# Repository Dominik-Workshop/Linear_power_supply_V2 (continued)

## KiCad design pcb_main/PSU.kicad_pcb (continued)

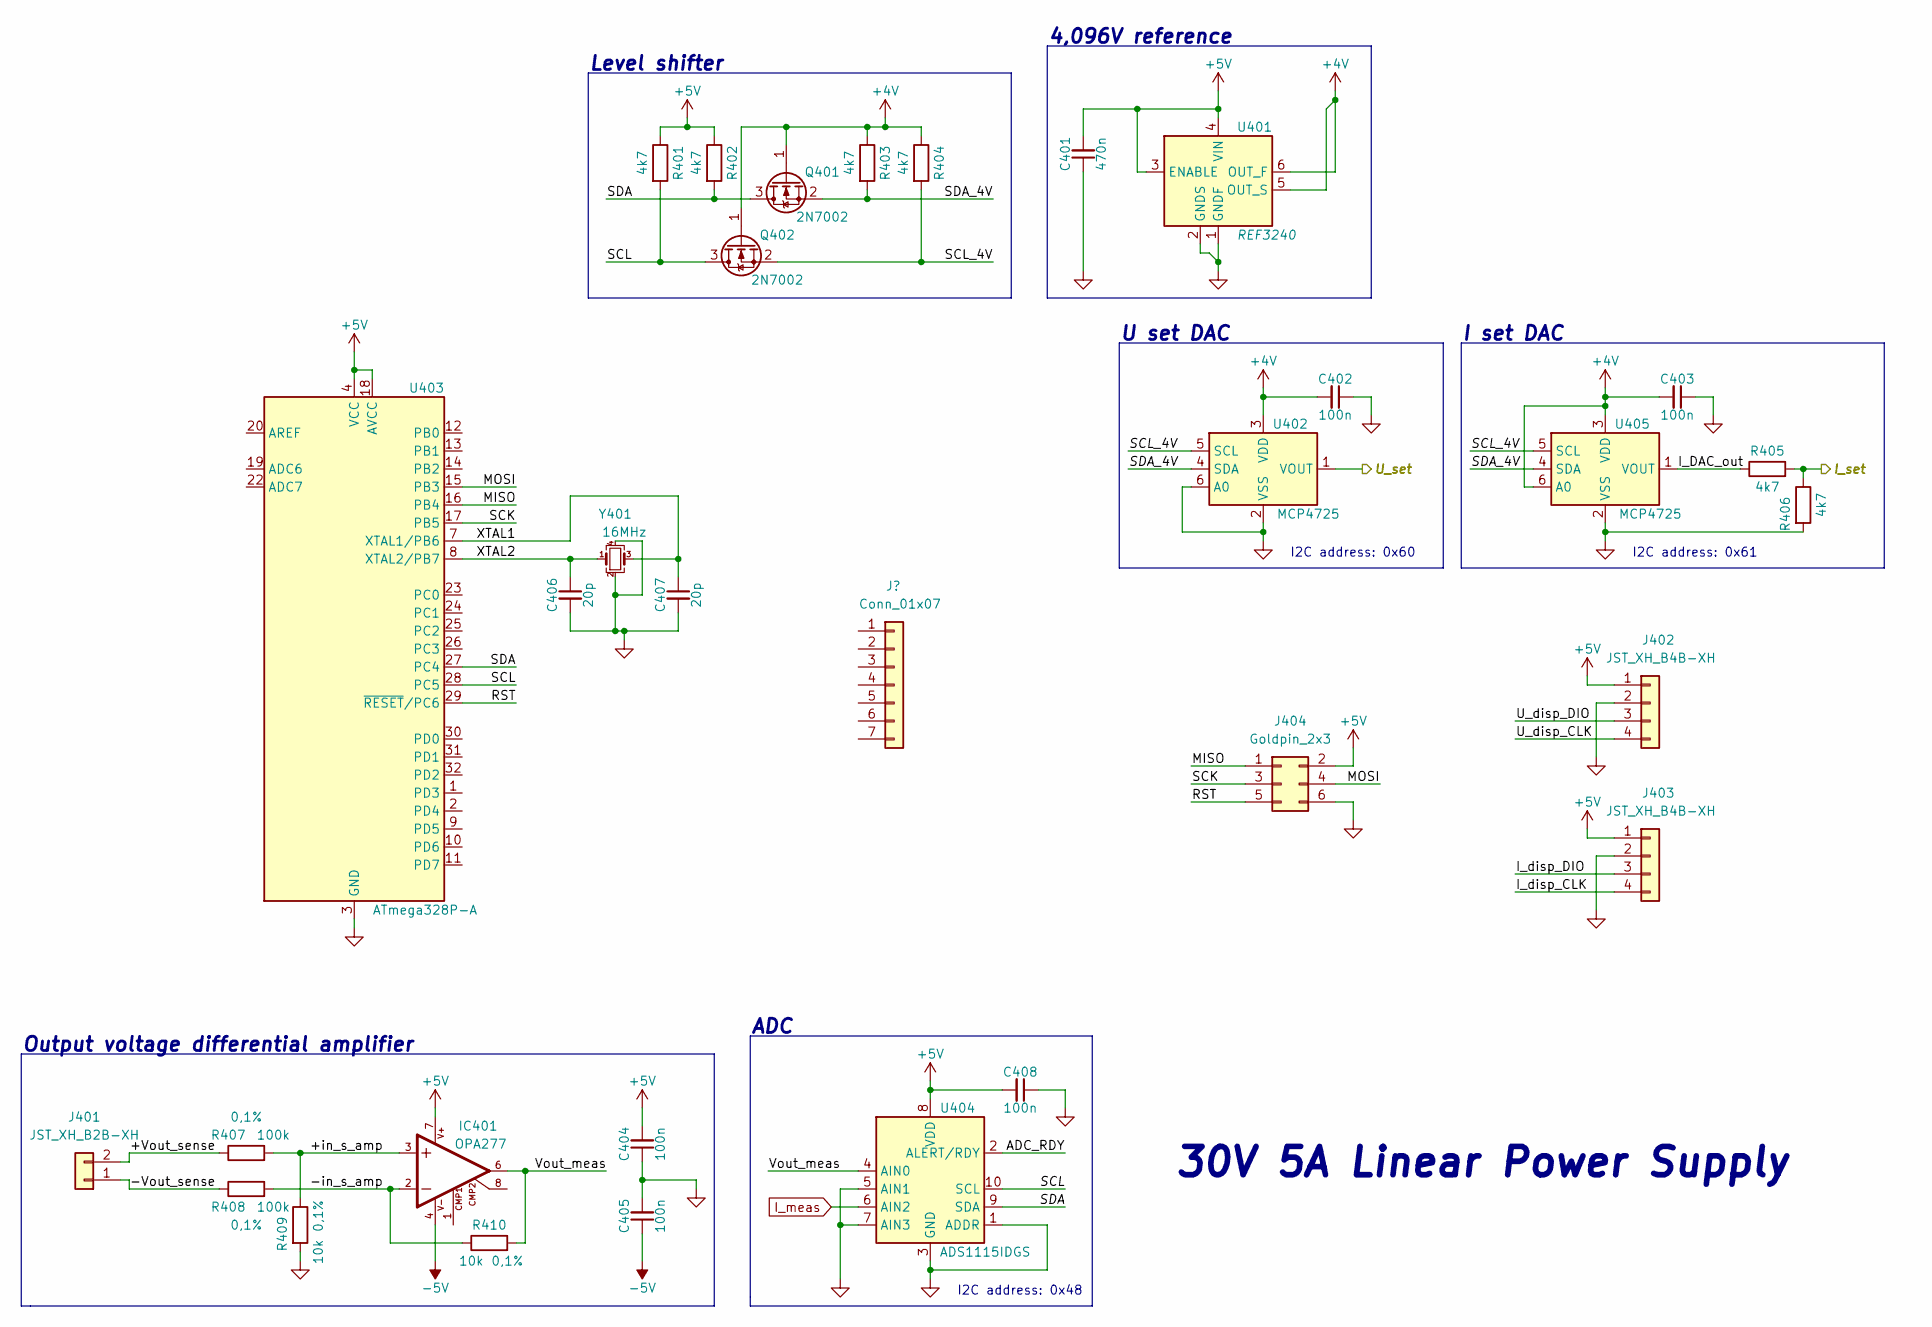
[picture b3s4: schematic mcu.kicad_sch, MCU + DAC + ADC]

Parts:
C401: 470n; C_0603_1608Metric
C402, C403, C404, C405, C408: 100n; C_0603_1608Metric
C406, C407: 20p; C_0603_1608Metric
IC401: OPA277; SO08
J401: JST_XH_B2B-XH; JST_XH_B2B-XH-A_1x02_P2.50mm_Vertical
J402, J403: JST_XH_B4B-XH; JST_XH_B4B-XH-A_1x04_P2.50mm_Vertical
J404: Goldpin_2x3; PinHeader_2x03_P2.54mm_Vertical
Q401, Q402: 2N7002; SOT-23
R401, R402, R403, R404, R405, R406: 4k7; R_0603_1608Metric
R407, R408: 100k; R_0603_1608Metric; Tolerance 0,1%
R409, R410: 10k; R_0603_1608Metric; Tolerance 0,1%
U401: REF3240; SOT-23-6
U402, U405: MCP4725; SOT-23-6
U403: ATmega328P-A; TQFP-32_7x7mm_P0.8mm
U404: ADS1115IDGS; TSSOP-10_3x3mm_P0.5mm
Y401: 16MHz; Crystal_SMD_SeikoEpson_TSX3225-4Pin_3.2x2.5mm

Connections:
+4V: C402.2, C403.2, Q401.1 (G), Q402.1 (G), R403.1, R404.1, U401.5 (OUT_S), U401.6 (OUT_F), U402.3 (VDD), U405.3 (VDD), U405.6 (A0)
+5V: C401.2, C404.2, C408.2, IC401.7, J402.1, J403.1, J404.2, R401.1, R402.1, U401.3 (ENABLE), U401.4 (VIN), U403.4 (VCC), U403.6 (VCC), U403.18 (AVCC), U404.8 (VDD); also elsewhere on the board
-5V: C405.1, IC401.4; also elsewhere on the board
/MCU/+Vout_sense: J401.2, R407.1
/MCU/+in_s_amp: IC401.3, R407.2, R409.1
/MCU/-Vout_sense: J401.1, R408.1
/MCU/-in_s_amp: IC401.2, R408.2, R410.1
/MCU/ADC_RDY: U404.2 (ALERT/RDY)
/MCU/I_DAC_out: R405.1, U405.1 (VOUT)
/MCU/I_disp_CLK: J403.4
/MCU/I_disp_DIO: J403.3
/MCU/I_set: R405.2, R406.1; also elsewhere on the board
/MCU/MISO: J404.1, U403.16 (PB4)
/MCU/MOSI: J404.4, U403.15 (PB3)
/MCU/RST: J404.5, U403.29 (~RESET/PC6)
/MCU/SCK: J404.3, U403.17 (PB5)
/MCU/SCL: Q402.3 (D), R401.2, U403.28 (PC5), U404.10 (SCL)
/MCU/SCL_4V: Q402.2 (S), R404.2, U402.5 (SCL), U405.5 (SCL)
/MCU/SDA: Q401.3 (D), R402.2, U403.27 (PC4), U404.9 (SDA)
/MCU/SDA_4V: Q401.2 (S), R403.2, U402.4 (SDA), U405.4 (SDA)
/MCU/U_disp_CLK: J402.4
/MCU/U_disp_DIO: J402.3
/MCU/U_set: U402.1 (VOUT); also elsewhere on the board
/MCU/Vout_meas: IC401.6, R410.2, U404.4 (AIN0)
/MCU/XTAL1: C407.1, U403.7 (XTAL1/PB6), Y401.3
/MCU/XTAL2: C406.1, U403.8 (XTAL2/PB7), Y401.1
GND: C401.1, C402.1, C403.1, C404.1, C405.2, C406.2, C407.2, C408.1, J402.2, J403.2, J404.6, R406.2, R409.2, U401.1 (GNDF), U401.2 (GNDS), U402.2 (VSS), U402.6 (A0), U403.3 (GND), U403.5 (GND), U403.21 (GND), U404.1 (ADDR), U404.3 (GND), U404.5 (AIN1), U404.7 (AIN3), U405.2 (VSS), Y401.2, Y401.4; also elsewhere on the board
I_meas: U404.6 (AIN2); also elsewhere on the board

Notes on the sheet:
U set DAC
4,096V reference
Output voltage differential amplifier
I set DAC
I2C address: 0x48
ADC
Level shifter
30V 5A Linear Power Supply
I2C address: 0x61
I2C address: 0x60

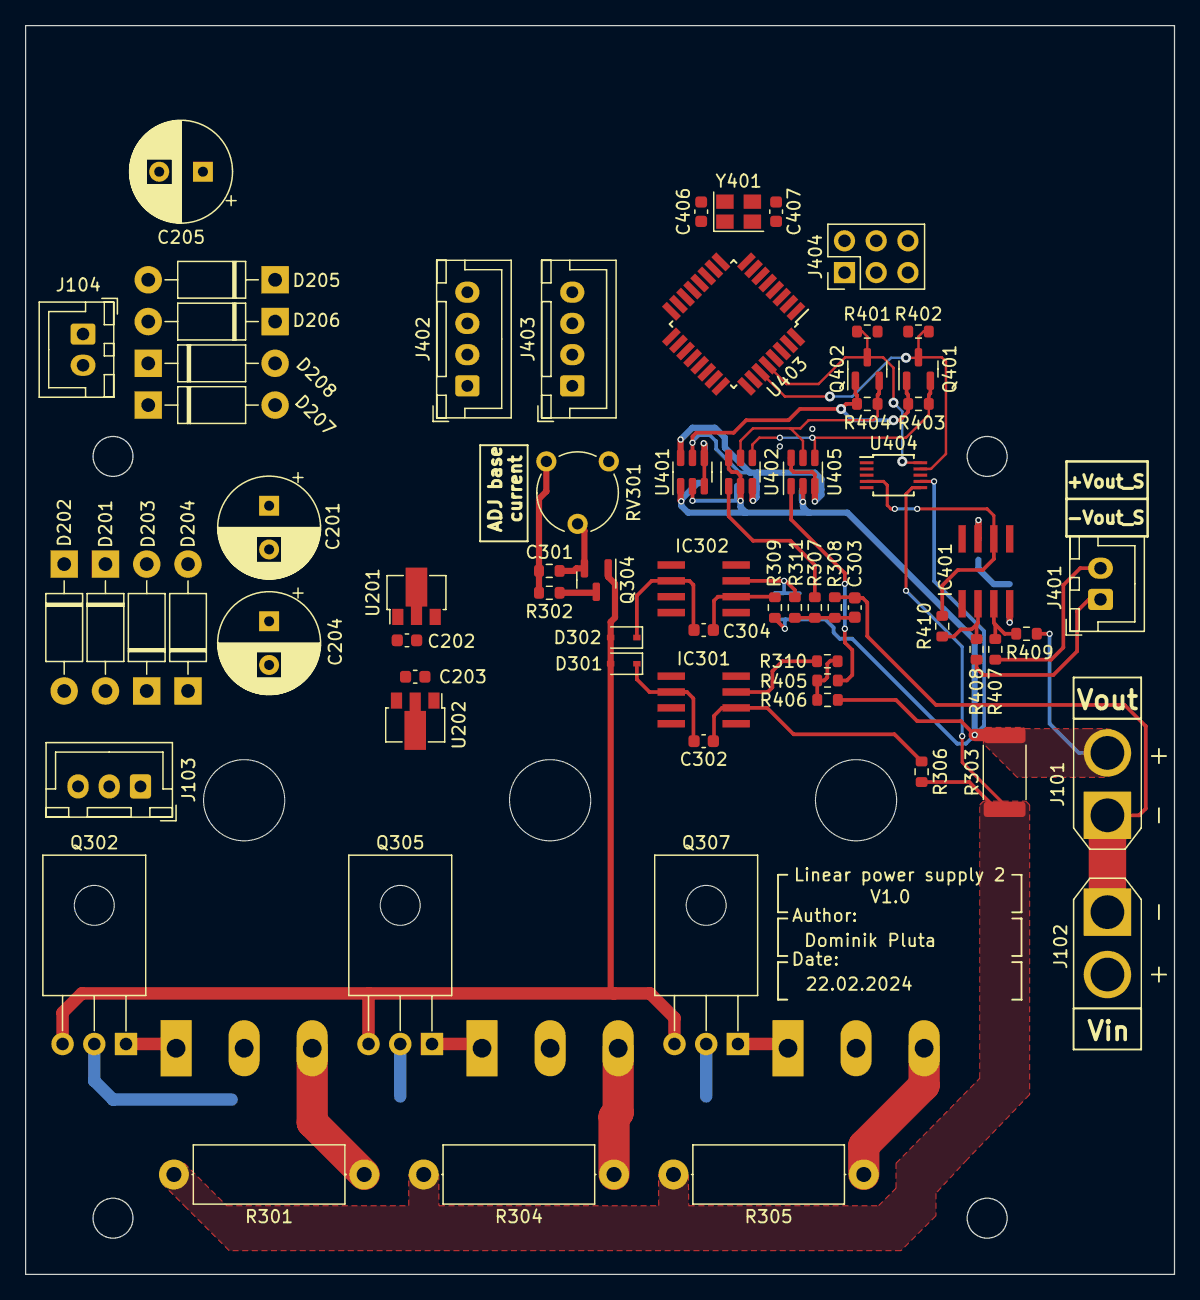
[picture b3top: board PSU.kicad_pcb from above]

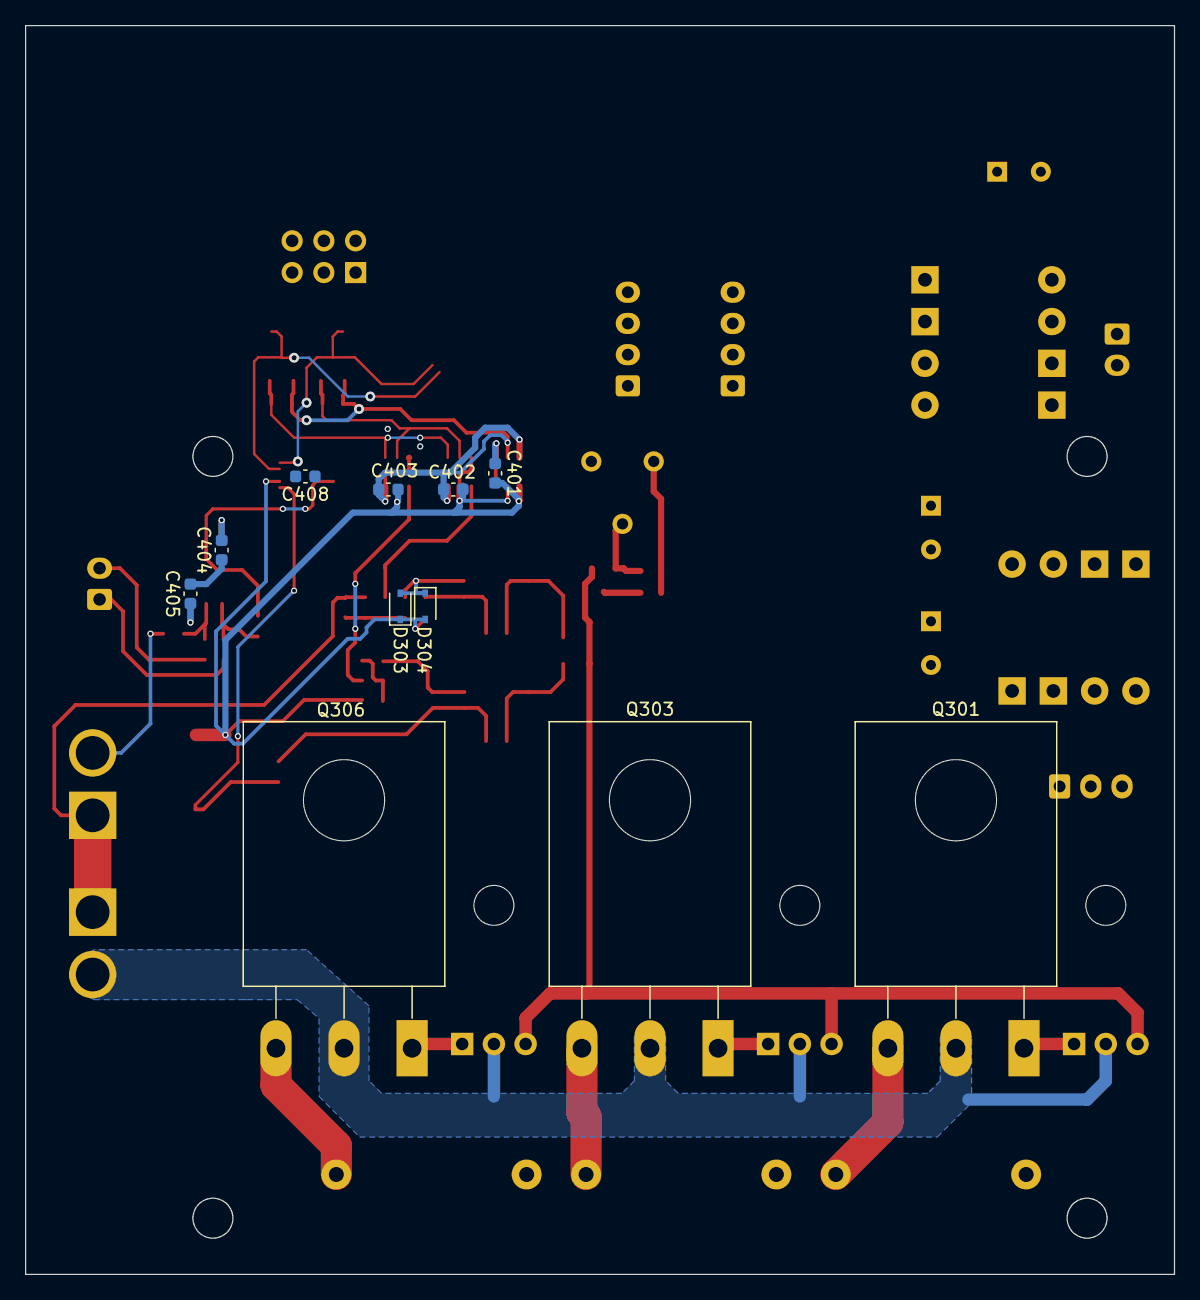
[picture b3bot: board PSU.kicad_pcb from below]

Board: 2 copper layers, 92.0 x 100.0 mm, 79 parts (11 on the bottom side), 47 nets.

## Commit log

2024-02-20 LTspice junk
2024-02-20 init
2024-02-20 project goals
2024-02-20 some sim
2024-02-20 datasheets
2024-02-20 pcb init
2024-02-20 kicad junk
2024-02-20 7 segment display tested, works
2024-02-20 display speed test
2024-02-21 transistors aligned
2024-02-21 +-5V reg
2024-02-21 hierarchical design
2024-02-22 power tracks routed
2024-02-23 most layout done
2024-02-25 kicad 7.0, new design
2024-02-25 design tool
2024-02-25 resize logo
2024-02-25 kicad 8.0
2024-02-25 resized logo
2024-02-26 most analog layout
2024-02-26 fin board
2024-02-26 centered pcb
2024-02-26 drc set, added icons, teardrops, info
2024-02-28 minor changes, final?
2024-03-16 minor changes
2024-03-16 add power board
2024-03-16 fix pictures
2024-03-16 add drill guide
2024-03-16 fif silkscreen
2024-03-16 remove unfinished stuff
2024-07-07 adjust emiter resistors values, correct relay2 silkscreen, add gerbers
2024-12-21 Add KiCad and LTspice unnecessary files to gitignore
2024-12-22 Add guide for heatsink drill holes
2024-12-22 Add power-board KiCad design
2024-12-22 Perform minor stylistic changes on power-board schematic, clear DRC
2024-12-22 Add KiCad and LTspice logo in README, update project description
2024-12-22 Add TO126, TO247, JST B4P and XT30 connector 3d models
2024-12-22 Add power-board gerber files zip
2024-12-22 Add screw symbol
2024-12-22 Add power-board top view render in README
2024-12-28 Rename power-board KiCad files
2024-12-28 Add CI for power-board PCB
2024-12-28 Add generated schematic PDF, necessary Gerber layers, and 3D model
2024-12-28 Change CI triggers to only manual triggeer
